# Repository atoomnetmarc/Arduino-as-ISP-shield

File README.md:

Quickly hacked together Arduino shield to program other Arduino's. Can also be used to program the old AT90S1200 microcontroller using avrdude. I used [AVRDUDESS 2.14](https://github.com/ZakKemble/AVRDUDESS/releases/tag/v2.14
) with avrdude 7.0.

Use the [ArduinoISP.ino](https://github.com/rsbohn/ArduinoISP/blob/master/ArduinoISP/ArduinoISP.ino) sketch to program your Arduino.

Use this define:
```#define USE_OLD_STYLE_WIRING```

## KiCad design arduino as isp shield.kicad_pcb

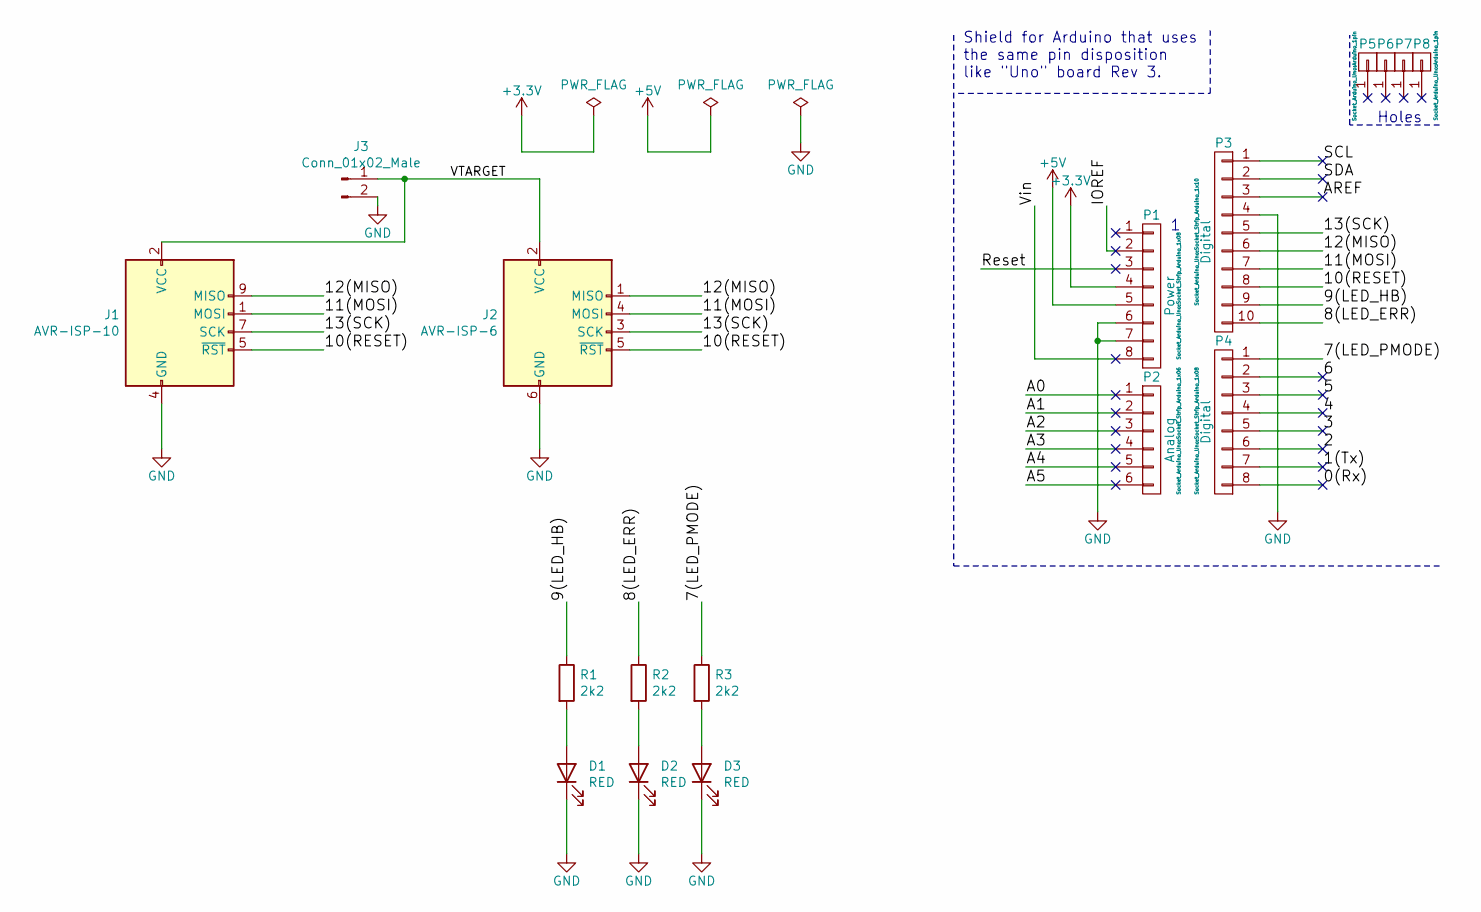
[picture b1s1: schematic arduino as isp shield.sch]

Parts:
D1, D2, D3: RED; LED_0805_2012Metric_Pad1.15x1.40mm_HandSolder
J1: AVR-ISP-10; IDC-Header_2x05_P2.54mm_Vertical
J2: AVR-ISP-6; IDC-Header_2x03_P2.54mm_Vertical
J3: Conn_01x02_Male; PinHeader_1x02_P2.54mm_Vertical
P1: Power; Socket_Strip_Arduino_1x08
P2: Analog; Socket_Strip_Arduino_1x06
P3: Digital; Socket_Strip_Arduino_1x10
P4: Digital; Socket_Strip_Arduino_1x08
P5, P6, P7, P8: CONN_01X01; Arduino_1pin
R1, R2, R3: 2k2; R_0805_2012Metric_Pad1.20x1.40mm_HandSolder

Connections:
+3V3: P1.4
+5V: P1.5
/0(Rx): P4.8
/1(Tx): P4.7
/2: P4.6
/3: P4.5
/4: P4.4
/5: P4.3
/6: P4.2
/7(LED_PMODE): P4.1, R3.1
/8(LED_ERR): P3.10, R2.1
/9(LED_HB): P3.9, R1.1
/10(RESET): J1.5 (~RST), J2.5 (~RST), P3.8
/11(MOSI): J1.1 (MOSI), J2.4 (MOSI), P3.7
/12(MISO): J1.9 (MISO), J2.1 (MISO), P3.6
/13(SCK): J1.7 (SCK), J2.3 (SCK), P3.5
/A0: P2.1
/A1: P2.2
/A2: P2.3
/A3: P2.4
/A4: P2.5
/A5: P2.6
/AREF: P3.3
/IOREF: P1.2
/Reset: P1.3
/SCL: P3.1
/SDA: P3.2
/VTARGET: J1.2 (VCC), J2.2 (VCC), J3.1
/Vin: P1.8
GND: D1.1 (K), D2.1 (K), D3.1 (K), J1.4 (GND), J1.6 (GND), J1.8 (GND), J1.10 (GND), J2.6 (GND), J3.2, P1.6, P1.7, P3.4
unnamed: D1.2 (A), R1.2
unnamed: D2.2 (A), R2.2
unnamed: D3.2 (A), R3.2

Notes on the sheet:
Holes
Shield for Arduino that uses the same pin disposition like "Uno" board Rev 3.

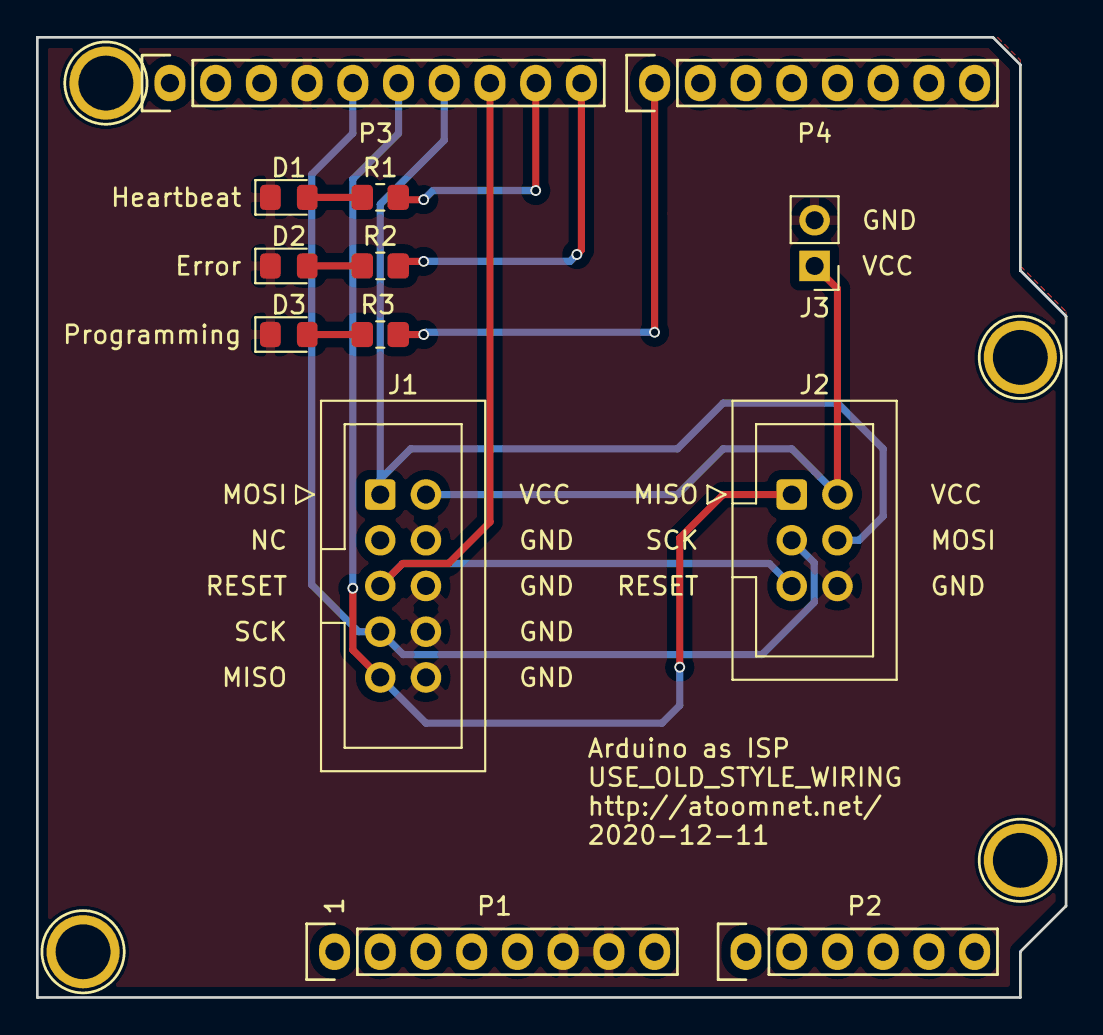
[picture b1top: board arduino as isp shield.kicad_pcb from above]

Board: 2 copper layers, 57.1 x 53.3 mm, 17 parts (0 on the bottom side), 12 nets.

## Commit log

2024-02-11 Add hint for avrdude version.

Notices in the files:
README.md:
License: Apache 2.0
